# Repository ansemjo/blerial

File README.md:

# BLErial v1

Carrier board for a transparent Bluetooth 5.0 BLE to UART bridge based on [JiNan Huamao HM-17 modules](http://www.jnhuamao.cn/bluetooth.asp).

There is loads of such modules on Aliexpress and elsewhere. However, what sets this module apart is the CR2032 coin cell battery on the bottom side, which provides enough juice to power the board before it is physically connected to any device – allowing you to connect the serial console already and capture the very first few packets, as soon as they come in. As soon as the target's VCC is connected, the 3.3 V regulator kicks in and a simple, very much *not* ideal diode "OR" picks the higher voltage of the two supplies. A [level shifter based on two N-channel MOSFETs](https://cdn-shop.adafruit.com/datasheets/AN10441.pdf) shifts the signal levels to whatever reference is given on VCC pin. Therefore the VCC connection is always required; maybe think of it more like a Vref.

## Bluetooth Modules

There are different modules which fit the footprint:

| Model | Bluetooth Version        |
| ----- | ------------------------ |
| HM-19 | BLE 5.0                  |
| HM-17 | BLE 5.0/4.2              |
| HM-13 | Dual Mode: 4.0 EDR + BLE |
| HM-11 | BLE 4.0                  |

I have also successfully connected a JDY-31. This required a glued-on plastic shim and some bodge wires but as long as you can connect `GND`, `VCC`, `RX`, `TX` and some sort of status `LED`, you should be good to go.

## Assembly

During assembly you can use the [interactive BOM `ibom.html`](https://ansemjo.github.io/blerial/ibom.html) to see where each component goes. Due to space constraints I ommitted reference designators in the silkscreen layer. :grimacing:

## Connection

* For the BLE modules, you can use [Jakeler/ble-serial](https://github.com/Jakeler/ble-serial) to create a `/tmp/ttyBLE` device, which you can then use with your favourite serial terminal.
* Dual Mode or older Bluetooth 2.0 RFCOMM devices can be connected with `rfcomm bind ...`.
* On Android devices, you can use the [Serial Bluetooth Terminal app](https://play.google.com/store/apps/details?id=de.kai_morich.serial_bluetooth_terminal) to connect both "classic" and LE modules.

## Images

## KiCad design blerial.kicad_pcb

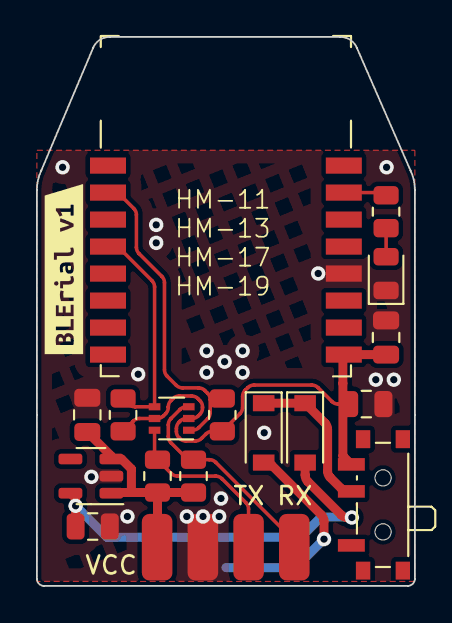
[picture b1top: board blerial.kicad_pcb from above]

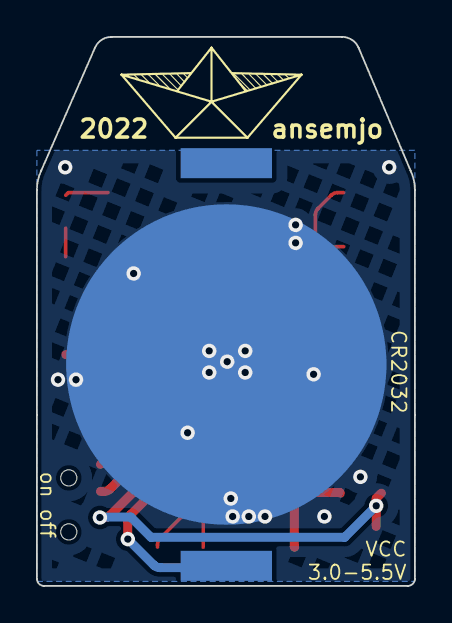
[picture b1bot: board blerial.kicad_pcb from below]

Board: 2 copper layers, 21.0 x 30.5 mm, 20 parts (2 on the bottom side), 12 nets.

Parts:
BT1: Coin Cell; BatteryHolder_Keystone_3034_1x20mm
C1, C2, C4: 1µF; C_0805_2012Metric
C3: 0.1µF; C_0805_2012Metric
D1: LED; LED_0805_2012Metric
D2, D3: 1N5819HW; D_SOD-123
J1: Header; PinHeader_1x04_P2.54mm_Horizontal
Q1: BSD840NH6327XTSA1; SOT-363_SC-70-6
R1: 2.2kΩ; R_0805_2012Metric
R2, R3, R4, R5: 10kΩ; R_0805_2012Metric
SW1: ON/OFF; SW_SPDT_PCM12
U1: HM-19
U2: MIC5504-3.3YM5; SOT-23-5
ahoi: 2022; ahoi
kibuzzard-622C9B09: G***; kibuzzard-622C9B09

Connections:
+3V3: C2.1, D2.2 (A), U2.5 (VOUT)
GND: BT1.2 (-), C1.2, C2.2, C3.2, C4.2, D1.1 (K), J1.3, U1.12 (GND), U2.2 (GND)
unnamed: BT1.1 (+), D3.2 (A)
unnamed: D1.2 (A), R1.1
unnamed: D2.1 (K), D3.1 (K), SW1.2 (B)
unnamed: R1.2, U1.15 (LED/PIO1)
RXD: Q1.4 (S), R4.2, U1.4 (RXD)
RXD_H: J1.1, Q1.3 (D), R5.2
TXD: Q1.1 (S), R2.2, U1.2 (TXD)
TXD_H: J1.2, Q1.6 (D), R3.2
VBUS: C1.1, J1.4, R3.1, R5.1, U2.1 (VIN), U2.3 (EN)
VCC: C3.1, C4.1, Q1.2 (G), Q1.5 (G), R2.1, R4.1, SW1.3 (C), U1.9 (VCC)

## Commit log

2022-02-21 begin tracking bluetooth serial board
2022-02-21 edit to switch between bat / 3.3 regulator
2022-02-21 add readme with a render
2022-03-11 rerouted for HM-19, but not very tidy
2022-03-12 finished redesign with 200µm net class, rotated battery
2022-03-12 small tweaks, correct diode and mosfet pns
2022-03-22 update readme with new pictures
2022-03-22 readme wording
2022-04-06 add new photos and amend readme
2022-09-09 add note about android app
2022-09-09 add link to online interactive bom
